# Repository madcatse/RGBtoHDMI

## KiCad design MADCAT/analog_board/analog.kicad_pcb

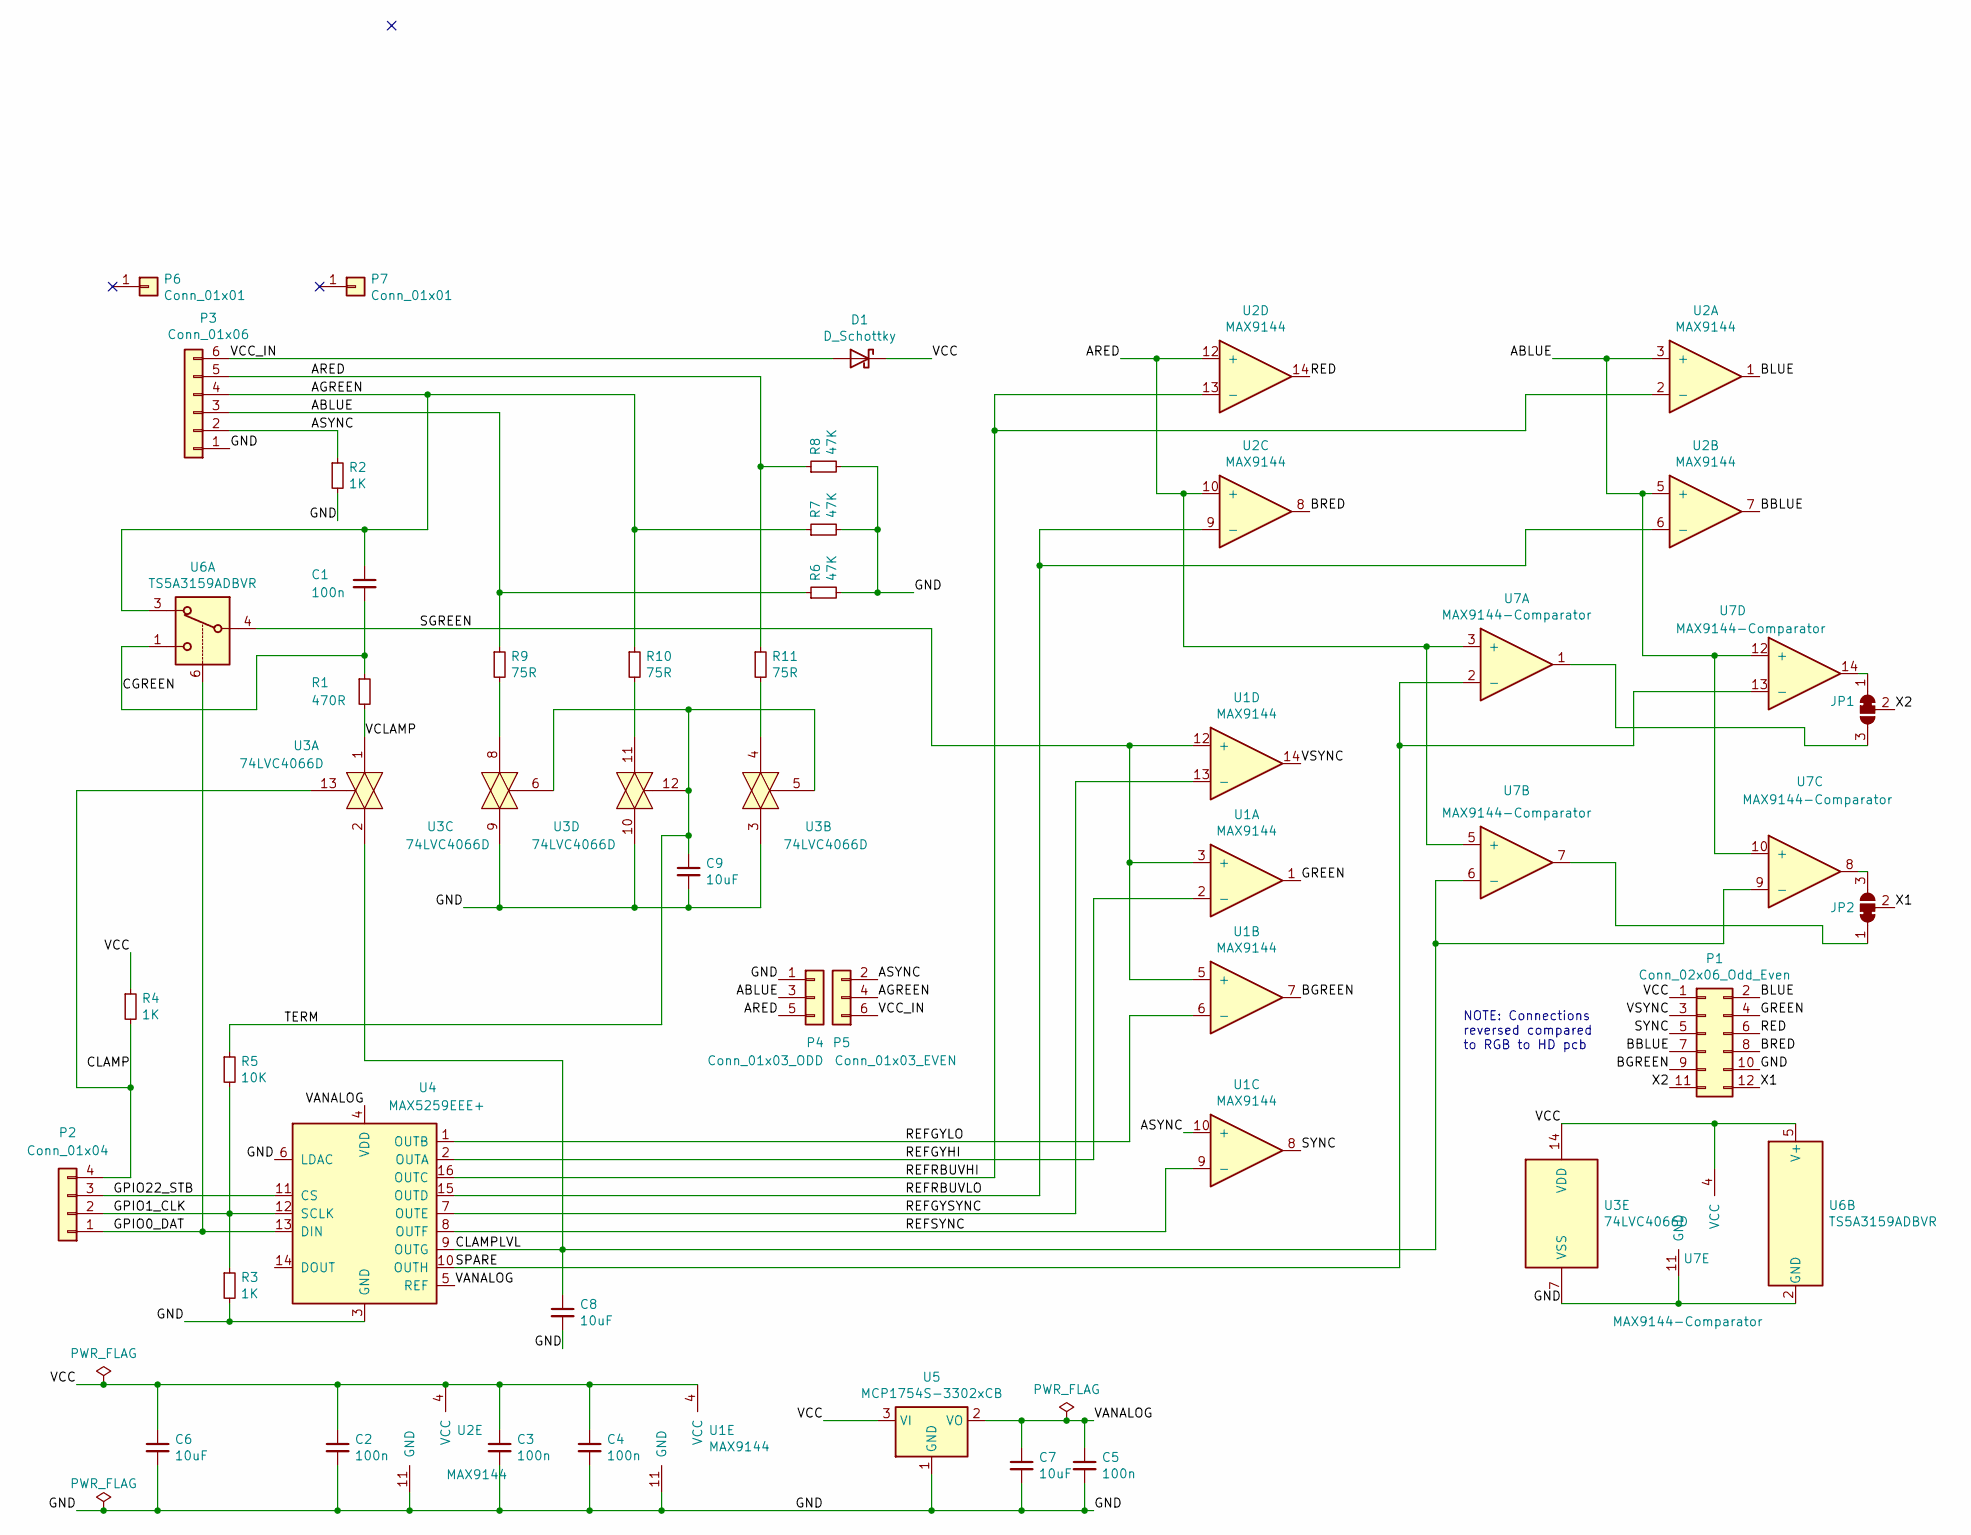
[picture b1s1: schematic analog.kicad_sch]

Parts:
C1, C2, C3, C4, C5: 100n; C_0805_2012Metric_Pad1.15x1.40mm_HandSolder
C6, C7, C8, C9: 10uF; C_0805_2012Metric_Pad1.15x1.40mm_HandSolder
D1: D_Schottky; D_SOD-123
JP1, JP2: SolderJumper_3_Bridged12; SolderJumper-3_P1.3mm_Bridged12_RoundedPad1.0x1.5mm
P1: Conn_02x06_Odd_Even; PinSocket_2x06_P2.54mm_Horizontal
P2: Conn_01x04; PinHeader_1x04_P2.54mm_Vertical
P3: Conn_01x06; Molex_PicoBlade_53048-0610_1x06_P1.25mm_Horizontal_Custom2
P4: Conn_01x03_ODD; Harwin_M20-89003xx_1x03_P2.54mm_Horizontal_Custom_ODD2
P5: Conn_01x03_EVEN; Harwin_M20-89003xx_1x03_P2.54mm_Horizontal_Custom_EVEN2
P6, P7: Conn_01x01; PinHeader_1x01_P2.54mm_Vertical
R1: 470R; R_0805_2012Metric_Pad1.15x1.40mm_HandSolder
R2, R3, R4: 1K; R_0805_2012Metric_Pad1.15x1.40mm_HandSolder
R5: 10K; R_0805_2012Metric_Pad1.15x1.40mm_HandSolder
R6, R7, R8: 47K; R_0805_2012Metric_Pad1.15x1.40mm_HandSolder
R9, R10, R11: 75R; R_0805_2012Metric_Pad1.15x1.40mm_HandSolder
U1, U2: MAX9144; SOIC-14_3.9x8.7mm_P1.27mm
U3: 74LVC4066D; SOIC-14_3.9x8.7mm_P1.27mm
U4: MAX5259EEE+; QSOP-16_3.9x4.9mm_P0.635mm
U5: MCP1754S-3302xCB; SOT-23_Handsoldering
U6: TS5A3159ADBVR; SOT-23-6_Handsoldering
U7: MAX9144-Comparator; SOIC-14_3.9x8.7mm_P1.27mm

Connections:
/ABLUE: P3.3, P4.3, R6.1, R9.1, U2.3 (+), U2.5 (+), U7.10 (+), U7.12 (+)
/AGREEN: C1.1, P3.4, P5.4, R7.1, R10.1, U6.3
/ARED: P3.5, P4.5, R8.1, R11.1, U2.10 (+), U2.12 (+), U7.3 (+), U7.5 (+)
/ASYNC: P3.2, P5.2, R2.1, U1.10 (+)
/BBLUE: P1.7, U2.7
/BGREEN: P1.9, U1.7
/BLUE: P1.2, U2.1
/BRED: P1.8, U2.8
/CGREEN: C1.2, R1.1, U6.1
/CLAMP: P2.4, R4.2, U3.13
/CLAMPLVL: C8.1, U3.2, U4.9 (OUTG), U7.6 (-), U7.9 (-)
/GND: C2.2, C3.2, C4.2, C5.2, C6.2, C7.2, C8.2, C9.2, P1.10, P3.1, P4.1, R2.2, R3.2, R6.2, R7.2, R8.2, U1.11 (GND), U2.11 (GND), U3.3, U3.7 (VSS), U3.9, U3.10, U4.3 (GND), U4.6 (LDAC), U5.1 (GND), U6.2 (GND), U7.11 (GND)
/GPIO0_DAT: P2.1, U4.13 (DIN), U6.6
/GPIO1_CLK: P2.2, R3.1, R5.2, U4.12 (SCLK)
/GPIO22_STB: P2.3, U4.11 (CS)
/GREEN: P1.4, U1.1
/RED: P1.6, U2.14
/REFGYHI: U1.2 (-), U4.2 (OUTA)
/REFGYLO: U1.6 (-), U4.1 (OUTB)
/REFGYSYNC: U1.13 (-), U4.7 (OUTE)
/REFRBUVHI: U2.2 (-), U2.13 (-), U4.16 (OUTC)
/REFRBUVLO: U2.6 (-), U2.9 (-), U4.15 (OUTD)
/REFSYNC: U1.9 (-), U4.8 (OUTF)
/SGREEN: U1.3 (+), U1.5 (+), U1.12 (+), U6.4
/SPARE: U4.10 (OUTH), U7.2 (-), U7.13 (-)
/SYNC: P1.5, U1.8
/TERM: C9.1, R5.1, U3.5, U3.6, U3.12
/VANALOG: C5.1, C7.1, U4.4 (VDD), U4.5 (REF), U5.2 (VO)
/VCC: C2.1, C3.1, C4.1, C6.1, D1.1 (K), P1.1, R4.1, U1.4 (VCC), U2.4 (VCC), U3.14 (VDD), U5.3 (VI), U6.5 (V+), U7.4 (VCC)
/VCC_IN: D1.2 (A), P3.6, P5.6
/VCLAMP: R1.2, U3.1
/VSYNC: P1.3, U1.14
/X1: JP2.2 (C), P1.12
/X2: JP1.2 (C), P1.11
unnamed: JP1.1 (A), U7.14
unnamed: JP1.3 (B), U7.1
unnamed: JP2.1 (A), U7.7
unnamed: JP2.3 (B), U7.8
unnamed: R9.2, U3.8
unnamed: R10.2, U3.11
unnamed: R11.2, U3.4

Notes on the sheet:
NOTE: Connections reversed compared to RGB to HD pcb

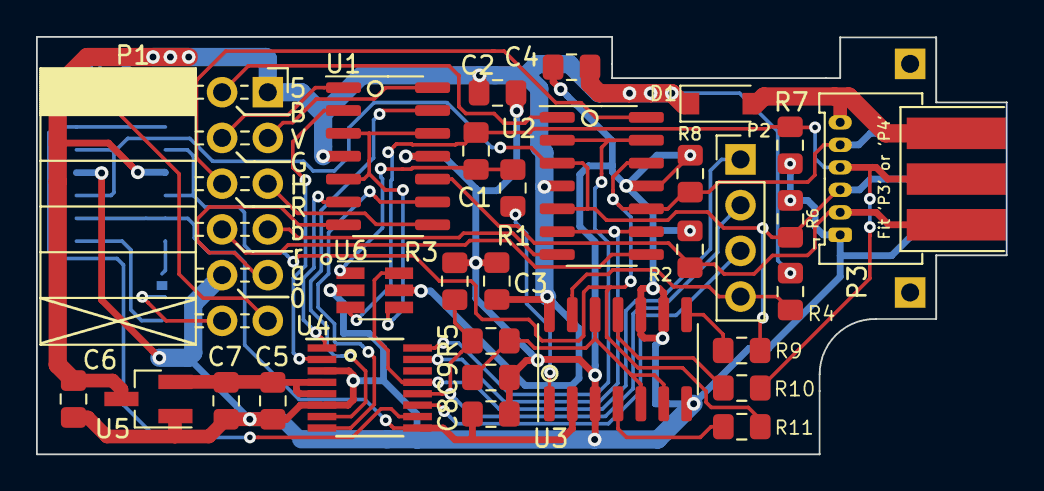
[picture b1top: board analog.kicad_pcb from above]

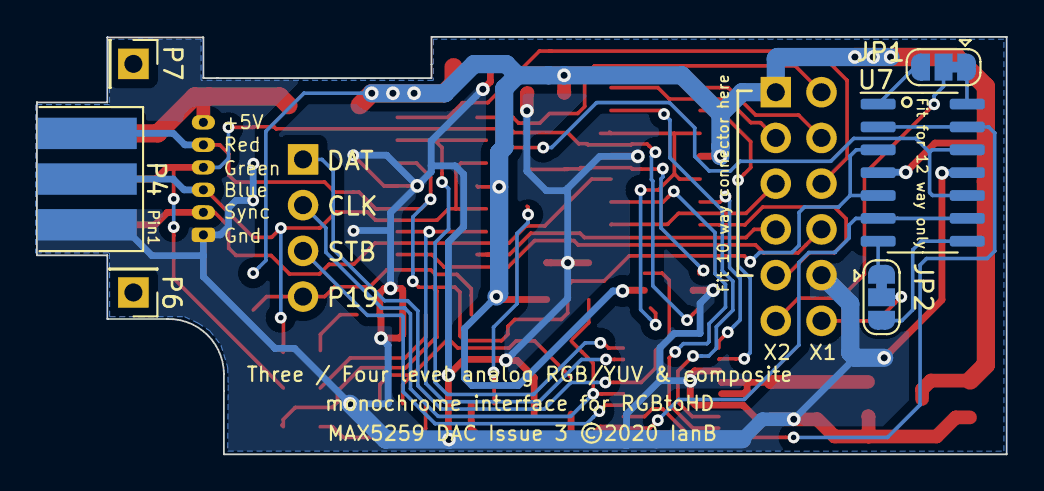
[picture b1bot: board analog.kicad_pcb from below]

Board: 2 copper layers, 53.9 x 23.2 mm, 37 parts (6 on the bottom side), 41 nets.

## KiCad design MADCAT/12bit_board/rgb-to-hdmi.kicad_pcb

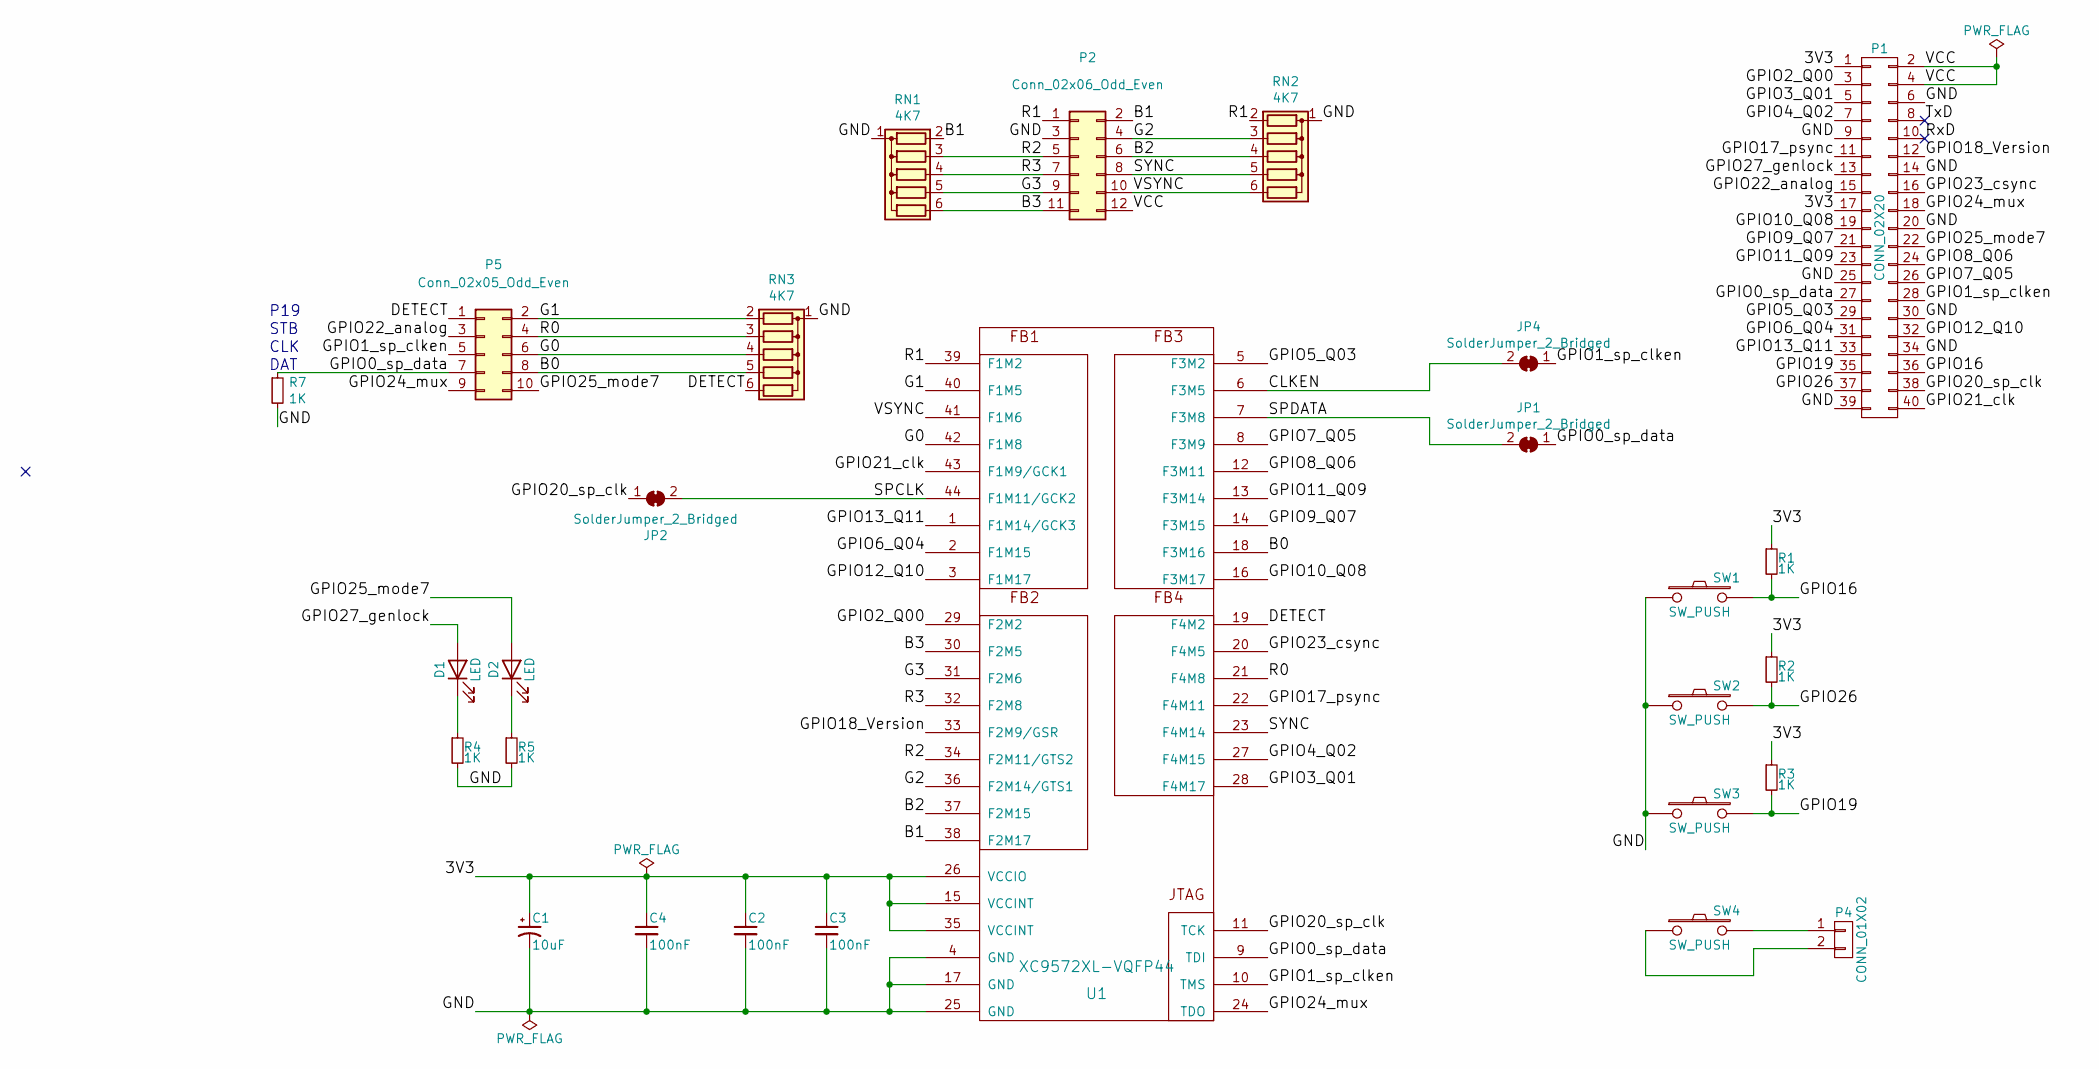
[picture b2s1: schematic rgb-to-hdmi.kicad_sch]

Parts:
C1: 10uF; C_0805_2012Metric_Pad1.15x1.40mm_HandSolder
C2, C3, C4: 100nF; C_0805_2012Metric_Pad1.15x1.40mm_HandSolder
D1, D2: LED; LED_D3.0mm
JP1, JP2, JP4: SolderJumper_2_Bridged; SolderJumper-2_P1.3mm_Bridged_RoundedPad1.0x1.5mm
P1: CONN_02X20; PinSocket_2x20_P2.54mm_Vertical_Custom
P2: Conn_02x06_Odd_Even; PinHeader_2x06_P2.54mm_Horizontal
P4: CONN_01X02; PinSocket_1x02_P2.54mm_Vertical_Custom
P5: Conn_02x05_Odd_Even; PinSocket_2x05_P2.54mm_Vertical
R1, R2, R3, R4, R5, R7: 1K; R_0805_2012Metric_Pad1.15x1.40mm_HandSolder
RN1, RN2, RN3: 4K7; R_Array_SIP6
SW1, SW2, SW3, SW4: SW_PUSH; SW_PUSH_6mm_H5mm
U1: XC9572XL-VQFP44; LQFP-44_10x10mm_P0.8mm

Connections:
/3V3: C1.1, C2.1, C3.1, C4.1, P1.1, P1.17, R1.1, R2.1, R3.1, U1.15 (VCCINT), U1.26 (VCCIO), U1.35 (VCCINT)
/B0: P5.8, RN3.5 (R4), U1.18 (F3M16)
/B1: P2.2, RN1.2 (R1), U1.38 (F2M17)
/B2: P2.6, RN2.4 (R3), U1.37 (F2M15)
/B3: P2.11, RN1.6 (R5), U1.30 (F2M5)
/CLKEN: JP4.2 (B), U1.6 (F3M5)
/DETECT: P5.1, RN3.6 (R5), U1.19 (F4M2)
/G0: P5.6, RN3.4 (R3), U1.42 (F1M8)
/G1: P5.2, RN3.2 (R1), U1.40 (F1M5)
/G2: P2.4, RN2.3 (R2), U1.36 (F2M14/GTS1)
/G3: P2.9, RN1.5 (R4), U1.31 (F2M6)
/GND: C1.2, C2.2, C3.2, C4.2, P1.6, P1.9, P1.14, P1.20, P1.25, P1.30, P1.34, P1.39, P2.3, R4.2, R5.2, R7.2, RN1.1 (common), RN2.1 (common), RN3.1 (common), SW1.1, SW2.1, SW3.1, U1.4 (GND), U1.17 (GND), U1.25 (GND)
/GPIO0_sp_data: JP1.1 (A), P1.27, P5.7, R7.1, U1.9 (TDI)
/GPIO1_sp_clken: JP4.1 (A), P1.28, P5.5, U1.10 (TMS)
/GPIO2_Q00: P1.3, U1.29 (F2M2)
/GPIO3_Q01: P1.5, U1.28 (F4M17)
/GPIO4_Q02: P1.7, U1.27 (F4M15)
/GPIO5_Q03: P1.29, U1.5 (F3M2)
/GPIO6_Q04: P1.31, U1.2 (F1M15)
/GPIO7_Q05: P1.26, U1.8 (F3M9)
/GPIO8_Q06: P1.24, U1.12 (F3M11)
/GPIO9_Q07: P1.21, U1.14 (F3M15)
/GPIO10_Q08: P1.19, U1.16 (F3M17)
/GPIO11_Q09: P1.23, U1.13 (F3M14)
/GPIO12_Q10: P1.32, U1.3 (F1M17)
/GPIO13_Q11: P1.33, U1.1 (F1M14/GCK3)
/GPIO16: P1.36, R1.2, SW1.2
/GPIO17_psync: P1.11, U1.22 (F4M11)
/GPIO18_Version: P1.12, U1.33 (F2M9/GSR)
/GPIO19: P1.35, R3.2, SW3.2
/GPIO20_sp_clk: JP2.1 (A), P1.38, U1.11 (TCK)
/GPIO21_clk: P1.40, U1.43 (F1M9/GCK1)
/GPIO22_analog: P1.15, P5.3
/GPIO23_csync: P1.16, U1.20 (F4M5)
/GPIO24_mux: P1.18, P5.9, U1.24 (TDO)
/GPIO25_mode7: D2.2 (A), P1.22, P5.10
/GPIO26: P1.37, R2.2, SW2.2
/GPIO27_genlock: D1.2 (A), P1.13
/R0: P5.4, RN3.3 (R2), U1.21 (F4M8)
/R1: P2.1, RN2.2 (R1), U1.39 (F1M2)
/R2: P2.5, RN1.3 (R2), U1.34 (F2M11/GTS2)
/R3: P2.7, RN1.4 (R3), U1.32 (F2M8)
/RxD: P1.10
/SPCLK: JP2.2 (B), U1.44 (F1M11/GCK2)
/SPDATA: JP1.2 (B), U1.7 (F3M8)
/SYNC: P2.8, RN2.5 (R4), U1.23 (F4M14)
/TxD: P1.8
/VCC: P1.2, P1.4, P2.12
/VSYNC: P2.10, RN2.6 (R5), U1.41 (F1M6)
unnamed: D1.1 (K), R4.1
unnamed: D2.1 (K), R5.1
unnamed: P4.1, SW4.2
unnamed: P4.2, SW4.1

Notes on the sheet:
DAT
STB
P19
CLK

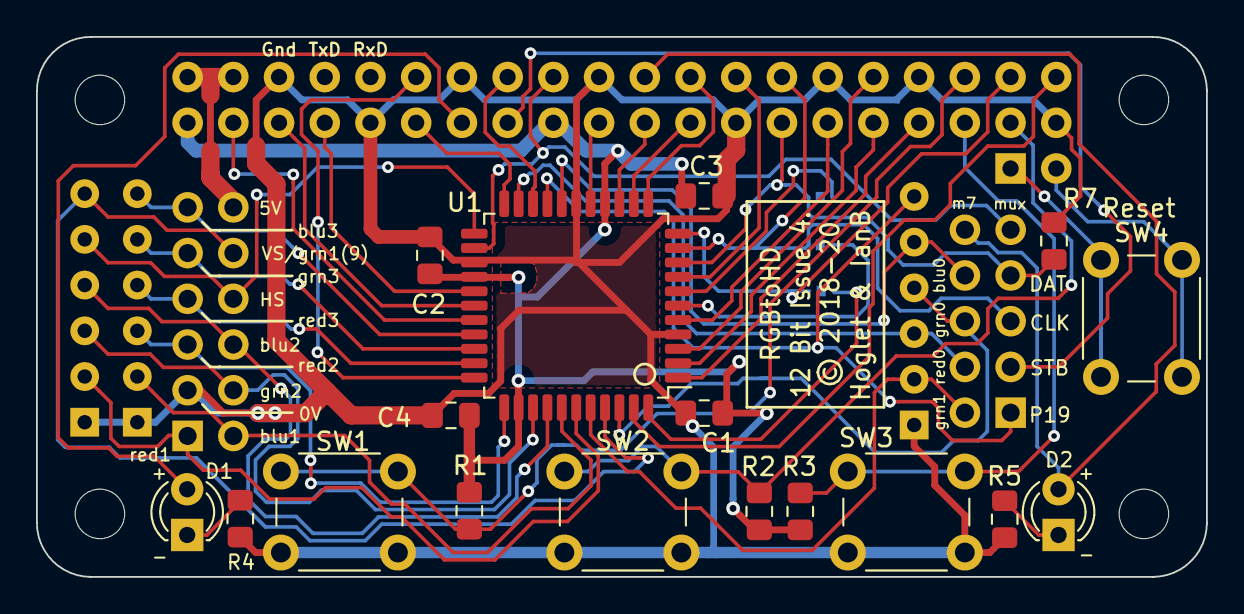
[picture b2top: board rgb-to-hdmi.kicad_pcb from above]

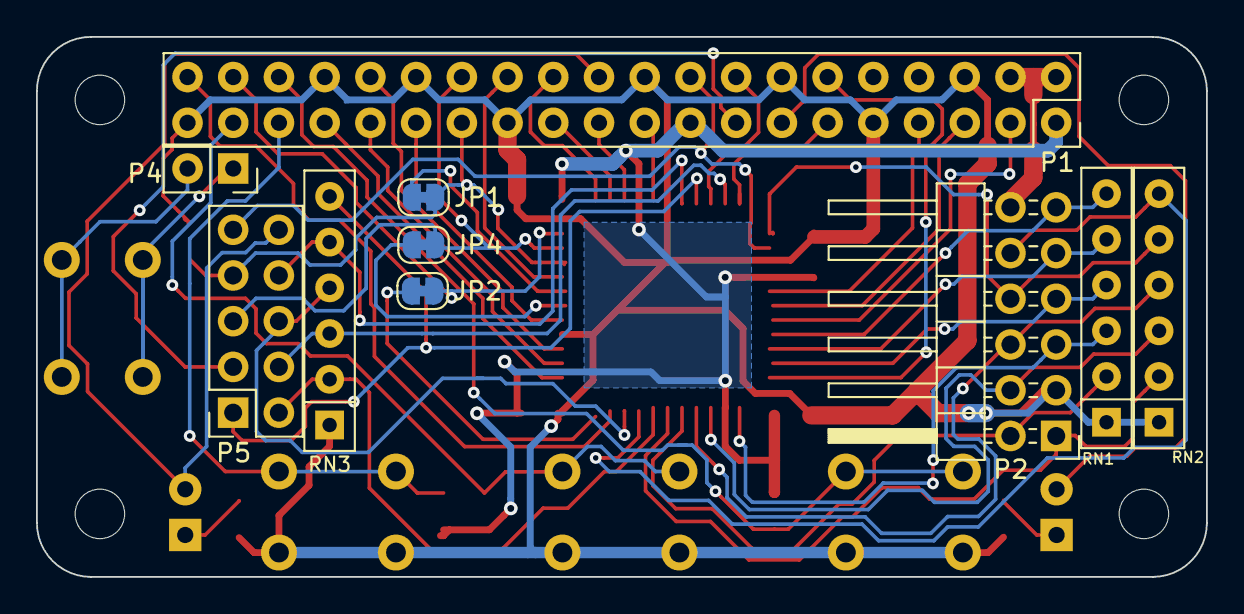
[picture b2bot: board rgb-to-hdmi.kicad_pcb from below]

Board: 2 copper layers, 65.0 x 30.0 mm, 27 parts (10 on the bottom side), 51 nets.

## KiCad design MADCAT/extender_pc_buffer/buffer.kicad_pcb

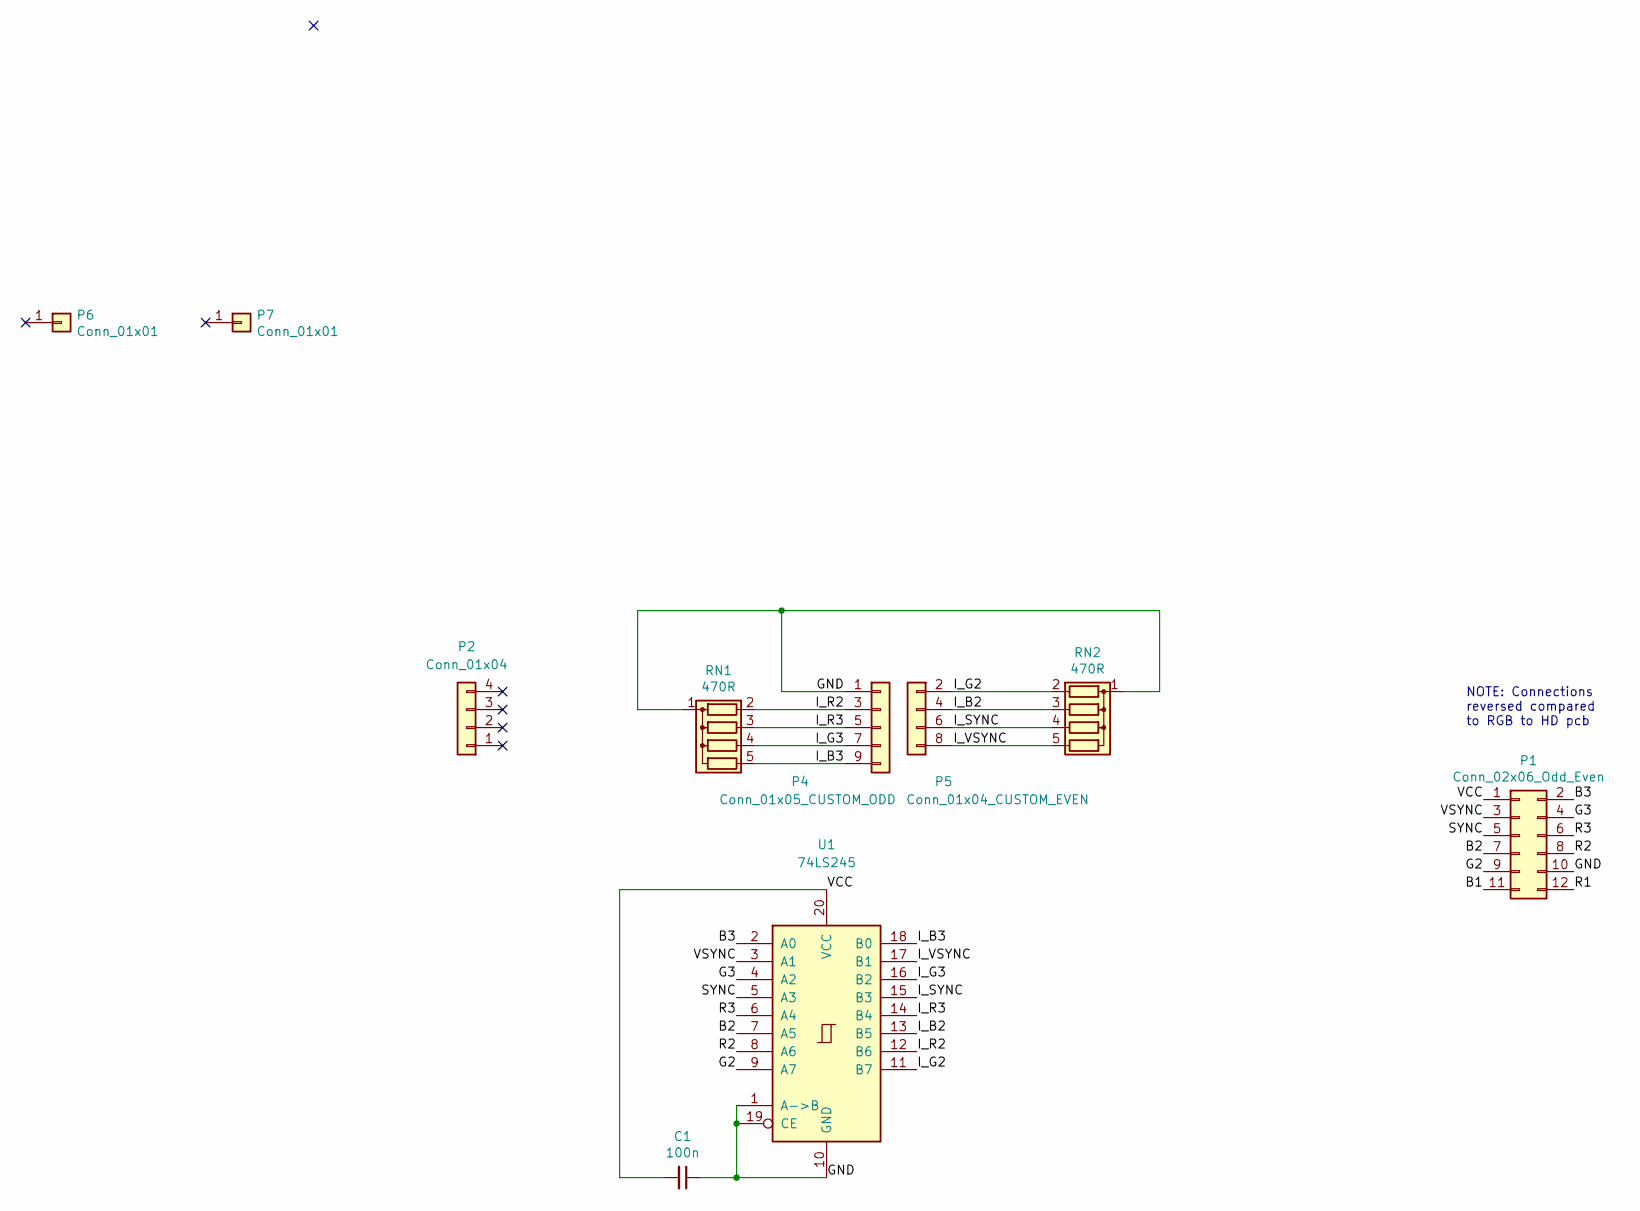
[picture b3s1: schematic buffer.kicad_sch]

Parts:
C1: 100n; C_0805_2012Metric_Pad1.15x1.40mm_HandSolder
P1: Conn_02x06_Odd_Even; PinSocket_2x06_P2.54mm_Horizontal
P2: Conn_01x04; PinHeader_1x04_P2.54mm_Vertical
P4: Conn_01x05_CUSTOM_ODD; Harwin_M20-89005xx_1x05_P2.54mm_Horizontal_CUSTOM_ODD
P5: Conn_01x04_CUSTOM_EVEN; Harwin_M20-89004xx_1x04_P2.54mm_Horizontal_CUSTOM_EVEN
P6, P7: Conn_01x01; PinHeader_1x01_P2.54mm_Vertical
RN1, RN2: 470R; R_Array_SIP5
U1: 74LS245; SOIC-20W_7.5x12.8mm_P1.27mm

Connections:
/B1: P1.11
/B2: P1.7, U1.7 (A5)
/B3: P1.2, U1.2 (A0)
/G2: P1.9, U1.9 (A7)
/G3: P1.4, U1.4 (A2)
/GND: C1.1, P1.10, P4.1, RN1.1 (common), RN2.1 (common), U1.1 (A->B), U1.10 (GND), U1.19 (CE)
/I_B2: P5.4, RN2.3 (R2), U1.13 (B5)
/I_B3: P4.9, RN1.5 (R4), U1.18 (B0)
/I_G2: P5.2, RN2.2 (R1), U1.11 (B7)
/I_G3: P4.7, RN1.4 (R3), U1.16 (B2)
/I_R2: P4.3, RN1.2 (R1), U1.12 (B6)
/I_R3: P4.5, RN1.3 (R2), U1.14 (B4)
/I_SYNC: P5.6, RN2.4 (R3), U1.15 (B3)
/I_VSYNC: P5.8, RN2.5 (R4), U1.17 (B1)
/R1: P1.12
/R2: P1.8, U1.8 (A6)
/R3: P1.6, U1.6 (A4)
/SYNC: P1.5, U1.5 (A3)
/VCC: C1.2, P1.1, U1.20 (VCC)
/VSYNC: P1.3, U1.3 (A1)

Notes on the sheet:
NOTE: Connections reversed compared to RGB to HD pcb

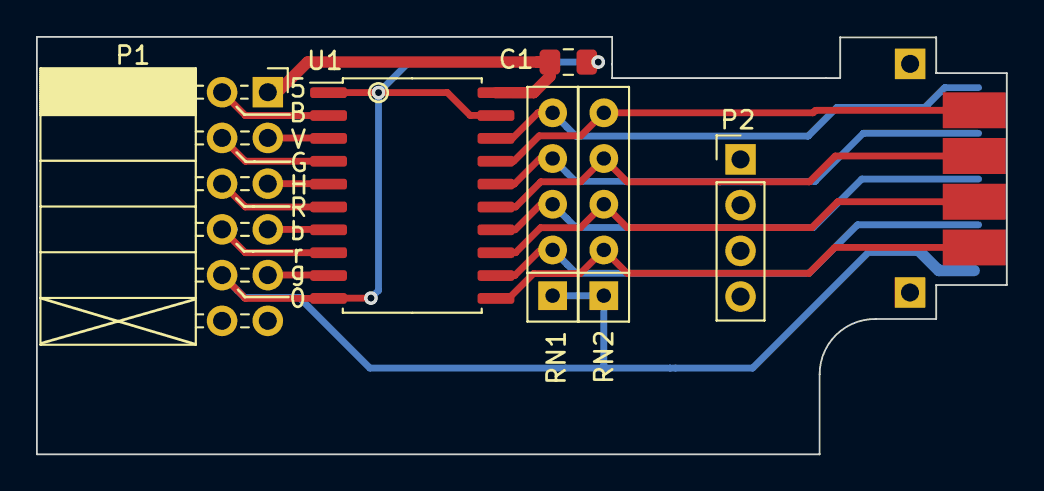
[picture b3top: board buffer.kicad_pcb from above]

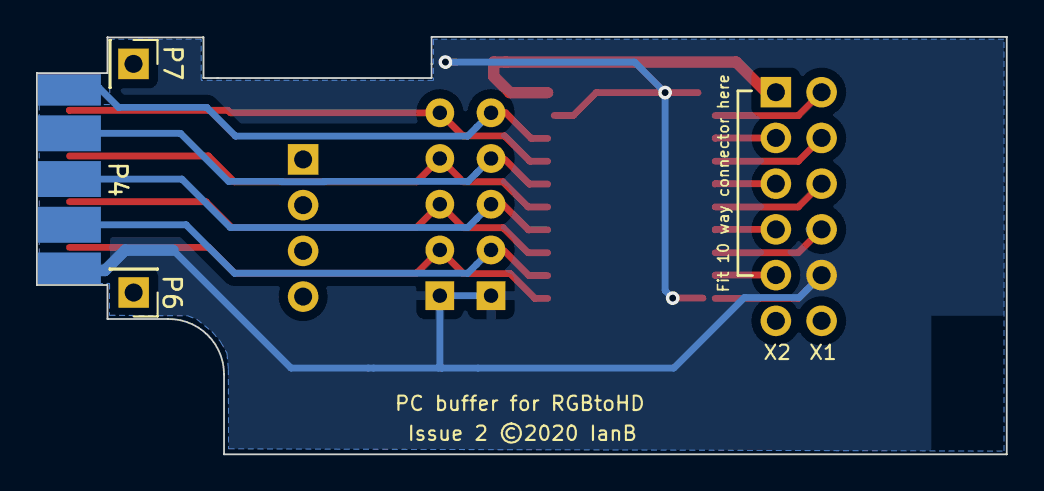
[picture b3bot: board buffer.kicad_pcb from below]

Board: 2 copper layers, 53.9 x 23.2 mm, 10 parts (3 on the bottom side), 18 nets.

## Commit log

2024-07-30 Preparing for assembly
2024-12-05 Backups

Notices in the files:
MADCAT/12bit_board/rgb-to-hdmi.kicad_pcb:
© 2018-20
MADCAT/analog_board/analog.kicad_pcb:
MAX5259 DAC Issue 3 ©2020 IanB
MADCAT/extender_pc_buffer/buffer.kicad_pcb:
Issue 2 ©2020 IanB
